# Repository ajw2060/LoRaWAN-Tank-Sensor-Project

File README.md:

# LoRaWAN-Tank-Sensor-Project
Project files including Schematics, PCB Layouts and code for Tank Sensor modules

The following components are included
1)  KiCad schematics and PCB layouts for the Pump Controller, Tank Top Sensor and Remote switch module.
2)  Micro python code for the Pycom LoPy4 based Tank Top Sensor
3)  Python code for the Raspberry Pi based Pump Controller
4)  Python code for the Raspberry Pi Zero W based remote switch module

The code has been zipped to keep the relevant files together.

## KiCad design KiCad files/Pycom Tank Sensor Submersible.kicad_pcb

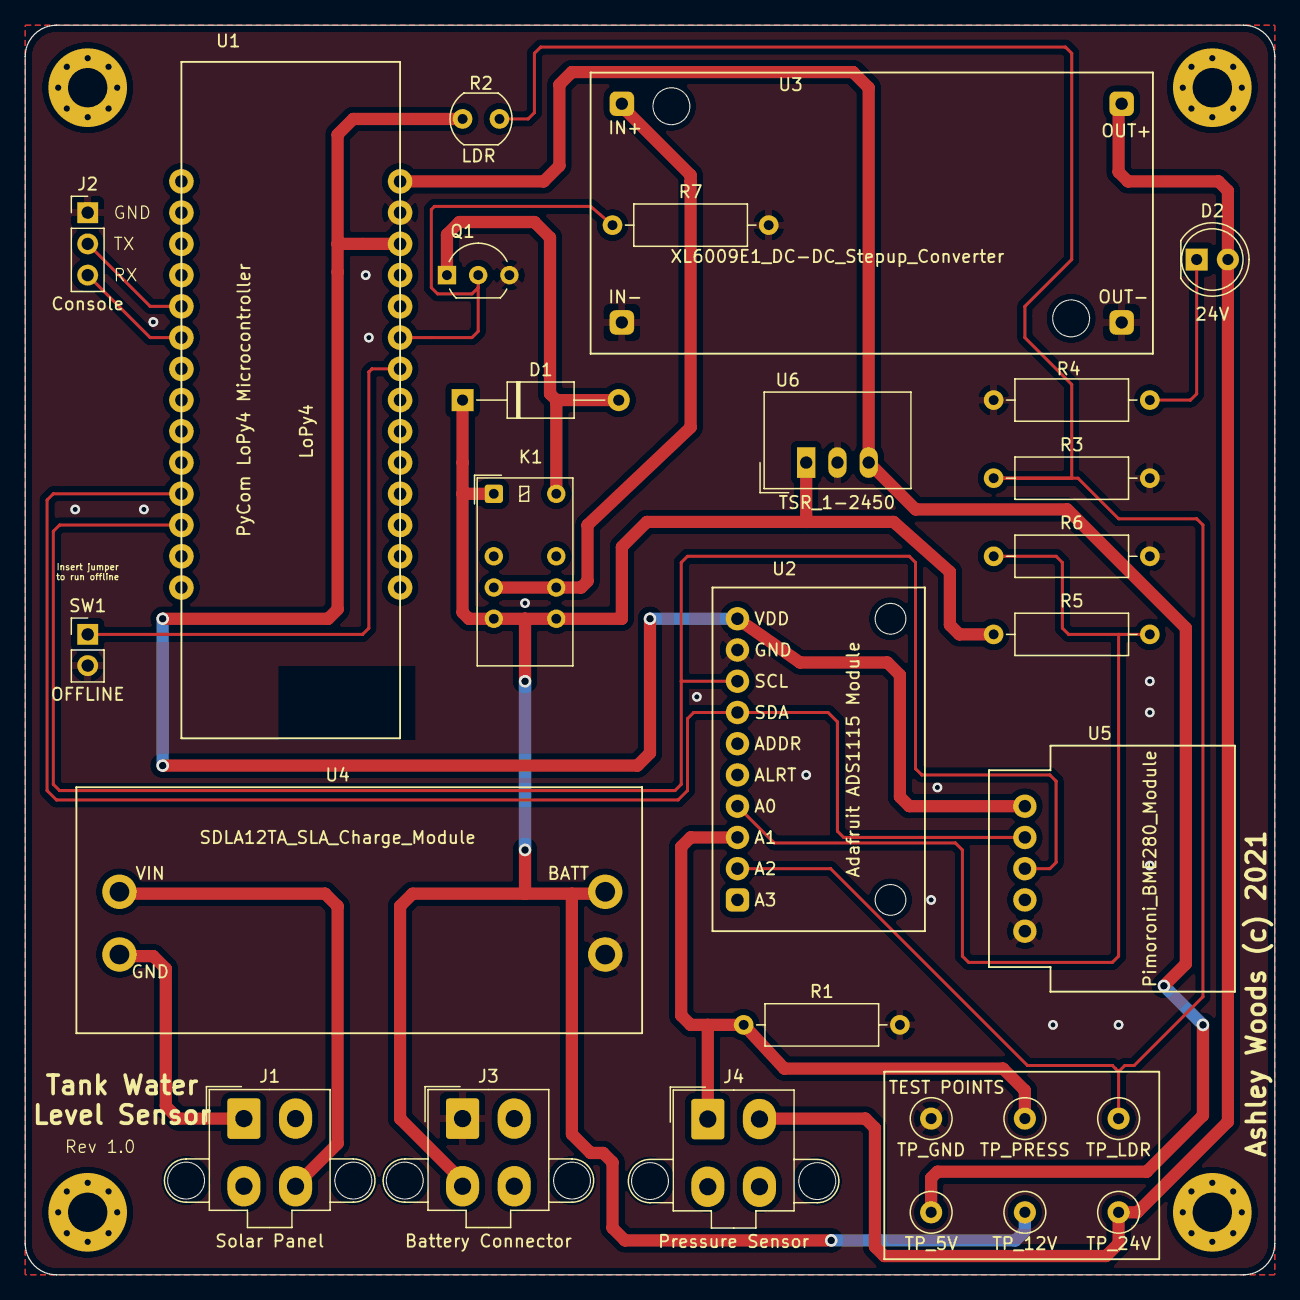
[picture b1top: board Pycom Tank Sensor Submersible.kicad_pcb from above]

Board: 2 copper layers, 101.6 x 101.6 mm, 32 parts (0 on the bottom side), 19 nets.

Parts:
D1: D; D_A-405_P12.70mm_Horizontal
D2: +24 LED; LED_D5.0mm
H1, H2, H3, H4: MountingHole; MountingHole_3.2mm_M3_Pad_Via
J1: Solar Panel; Molex_Mini-Fit_Jr_5566-04A2_2x02_P4.20mm_Vertical
J2: Console; PinHeader_1x03_P2.54mm_Vertical
J3: Battery Connector; Molex_Mini-Fit_Jr_5566-04A2_2x02_P4.20mm_Vertical
J4: Pressure Sensor; Molex_Mini-Fit_Jr_5566-04A2_2x02_P4.20mm_Vertical
J5: TP_GND; TestPoint_Loop_D2.60mm_Drill0.9mm_Beaded
J6: TP_5V; TestPoint_Loop_D2.60mm_Drill0.9mm_Beaded
J7: TP_12V; TestPoint_Loop_D2.60mm_Drill0.9mm_Beaded
J8: TP_24V; TestPoint_Loop_D2.60mm_Drill0.9mm_Beaded
J9: TP_PRESS; TestPoint_Loop_D2.60mm_Drill0.9mm_Beaded
J10: TP_LDR; TestPoint_Loop_D2.60mm_Drill0.9mm_Beaded
K1: EC2-12NU; Relay_DPDT_Kemet_EC2
Q1: BS170; TO-92_Inline_Wide
R1: 100R; R_Axial_DIN0309_L9.0mm_D3.2mm_P12.70mm_Horizontal
R2: LDR; R_LDR_5.0x4.1mm_P3mm_Vertical
R3: 1K; R_Axial_DIN0309_L9.0mm_D3.2mm_P12.70mm_Horizontal
R4: 1.5K; R_Axial_DIN0309_L9.0mm_D3.2mm_P12.70mm_Horizontal
R5: 15K; R_Axial_DIN0309_L9.0mm_D3.2mm_P12.70mm_Horizontal
R6: 4.7K; R_Axial_DIN0309_L9.0mm_D3.2mm_P12.70mm_Horizontal
R7: 10K; R_Axial_DIN0309_L9.0mm_D3.2mm_P12.70mm_Horizontal
SW1: OFFLINE; PinHeader_1x02_P2.54mm_Vertical
U1: LoPy4; LoPy_with_headers
U2: Adafruit_ADS1115_Module
U3: XL6009E1_DC-DC_Stepup_Converter; XL6009E1_DC-DC_Converter
U4: SDLA12TA_SLA_Charge_Module; SDLA12TA_Module
U5: Pimoroni_BME280_Module; Pimoroni BME280 Module
U6: TSR_1-2450; Converter_DCDC_TRACO_TSR-1_THT

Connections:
3v3: R2.1, U1.26, U2.10, U5.1
BATTERY+12: D1.1, J3.3, J7.1, K1.1, K1.5, K1.8, R5.1, U4.4, U6.1
BATTLEVEL_SENSE: R5.2, R6.1, U2.4
BOOST24POS: D2.2, J4.2, J8.1, U3.3
BOOST_ENABLE: Q1.2, R7.1, U1.23
BOOST_SUPPLY: K1.4, K1.9, U3.1
BOOST_SWITCH: D1.2, K1.12, Q1.1
CONSOLE_RX: J2.3, U1.6
CONSOLE_TX: J2.2, U1.5
GND: J2.1, J3.1, J5.1, Q1.3, R1.2, R3.2, R4.2, R6.2, R7.2, SW1.2, U1.27, U2.9, U3.2, U3.4, U4.3, U5.5, U6.2
LDR_SENSE: J10.1, R2.2, R3.1, U2.2
unnamed: D2.1, R4.1
OFFLINE_MODE: SW1.1, U1.22
PANEL_NEG: J1.1, U4.2
PANEL_POS: J1.4, U4.1
PRESS_SENSE: J4.1, J9.1, R1.1, U2.3
SCL: U1.12, U2.8, U5.3
SDA: U1.11, U2.7, U5.2
VCC: J6.1, U1.28, U6.3

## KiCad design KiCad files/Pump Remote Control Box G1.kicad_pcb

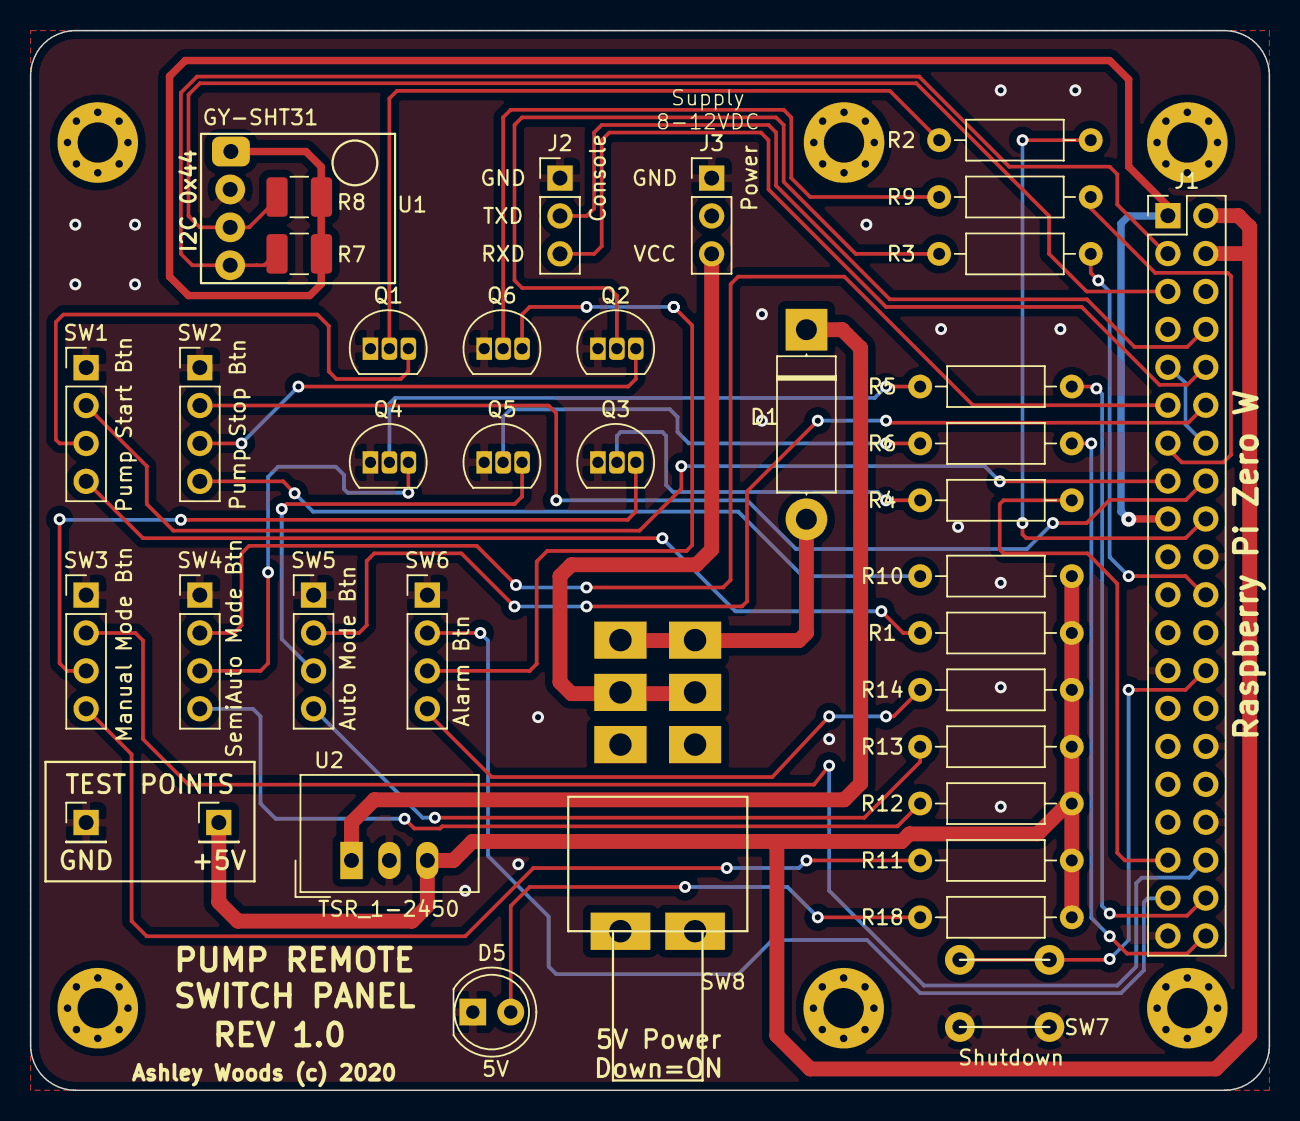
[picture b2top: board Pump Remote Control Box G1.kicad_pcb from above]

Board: 2 copper layers, 83.0 x 71.0 mm, 44 parts (0 on the bottom side), 42 nets.

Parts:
D1: D; D_5W_P12.70mm_Horizontal
D5: 5V; LED_D5.0mm
H1, H2, H3, H4, H5, H6: Mount; MountingHole_2.7mm_M2.5_Pad_Via
J1: Raspberry_Pi_2_3; PinHeader_2x20_P2.54mm_Vertical
J2: Serial Console Connector; PinHeader_1x03_P2.54mm_Vertical
J3: Power Input Connector; PinHeader_1x03_P2.54mm_Vertical
Q1, Q2, Q3, Q4, Q5, Q6: P2N2222A; TO-92L_Inline
R1, R10, R11, R12, R13, R14, R18: 220R; R_Axial_DIN0207_L6.3mm_D2.5mm_P10.16mm_Horizontal
R2, R3, R4, R5, R6, R9: 4k3; R_Axial_DIN0207_L6.3mm_D2.5mm_P10.16mm_Horizontal
R7, R8: 10K; R_1210_3225Metric_Pad1.42x2.65mm_HandSolder
SW1: Pump Start Button; PinHeader_1x04_P2.54mm_Vertical
SW2: Pump Stop Button; PinHeader_1x04_P2.54mm_Vertical
SW3: Manual Mode Button; PinHeader_1x04_P2.54mm_Vertical
SW4: Semiauto Mode Button; PinHeader_1x04_P2.54mm_Vertical
SW5: Auto Mode Button; PinHeader_1x04_P2.54mm_Vertical
SW6: Alarm Button; PinHeader_1x04_P2.54mm_Vertical
SW7: Shutdown; PCB Switch RS 479-1413
SW8: SW_DPDT; Switch DPDT Jaycar ST0365
TP1: TP GND; PinHeader_1x01_P2.54mm_Vertical
TP2: TP +5V; PinHeader_1x01_P2.54mm_Vertical
U1: GY_SHT31-Breakout-pycom; GY_SHT31_Breakout
U2: TSR_1-2450; Converter_DCDC_TRACO_TSR-1_THT

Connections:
3v3: J1.1, J1.17, R7.1, R8.1, U1.1
5V: J1.2, J1.4, R1.1, R10.1, R11.1, R12.1, R13.1, R14.1, R18.2, TP2.1, U2.3
Alarm_Button: J1.37, SW6.2
Alarm_Button_LED: J1.13, R9.2
Auto_Mode_Button: J1.12, SW5.2
Auto_Mode_Button_LED: J1.40, R6.2
GND: D5.1, J1.6, J1.9, J1.14, J1.20, J1.25, J1.30, J1.34, J1.39, J2.1, J3.1, Q1.1, Q2.1, Q3.1, Q4.1, Q5.1, Q6.1, SW1.1, SW2.1, SW3.1, SW4.1, SW5.1, SW6.1, SW7.3, SW7.4, TP1.1, U1.2, U2.2
Manual_Mode_Button: J1.36, SW3.2
Manual_Mode_Button_LED: J1.35, R4.2
unnamed: D1.1, U2.1
unnamed: D1.2, SW8.1, SW8.4
unnamed: D5.2, R18.1
unnamed: J3.3, SW8.2, SW8.5
unnamed: Q1.2, R2.1
unnamed: Q1.3, SW1.3
unnamed: Q2.2, R3.1
unnamed: Q2.3, SW2.3
unnamed: Q3.2, R4.1
unnamed: Q3.3, SW3.3
unnamed: Q4.2, R5.1
unnamed: Q4.3, SW4.3
unnamed: Q5.2, R6.1
unnamed: Q5.3, SW5.3
unnamed: Q6.2, R9.1
unnamed: Q6.3, SW6.3
unnamed: R1.2, SW1.4
unnamed: R10.2, SW2.4
unnamed: R11.2, SW3.4
unnamed: R12.2, SW4.4
unnamed: R13.2, SW5.4
unnamed: R14.2, SW6.4
Pump_Start_Button: J1.15, SW1.2
Pump_Start_Button_LED: J1.18, R2.2
Pump_Stop_Button: J1.16, SW2.2
Pump_Stop_Button_LED: J1.22, R3.2
RXD: J1.10, J2.3
SCL: J1.5, R8.2, U1.3
SDA: J1.3, R7.2, U1.4
SHUTDOWN: J1.26, SW7.1, SW7.2
Semiauto_Mode_Button: J1.11, SW4.2
Semiauto_Mode_Button_LED: J1.38, R5.2
TXD: J1.8, J2.2

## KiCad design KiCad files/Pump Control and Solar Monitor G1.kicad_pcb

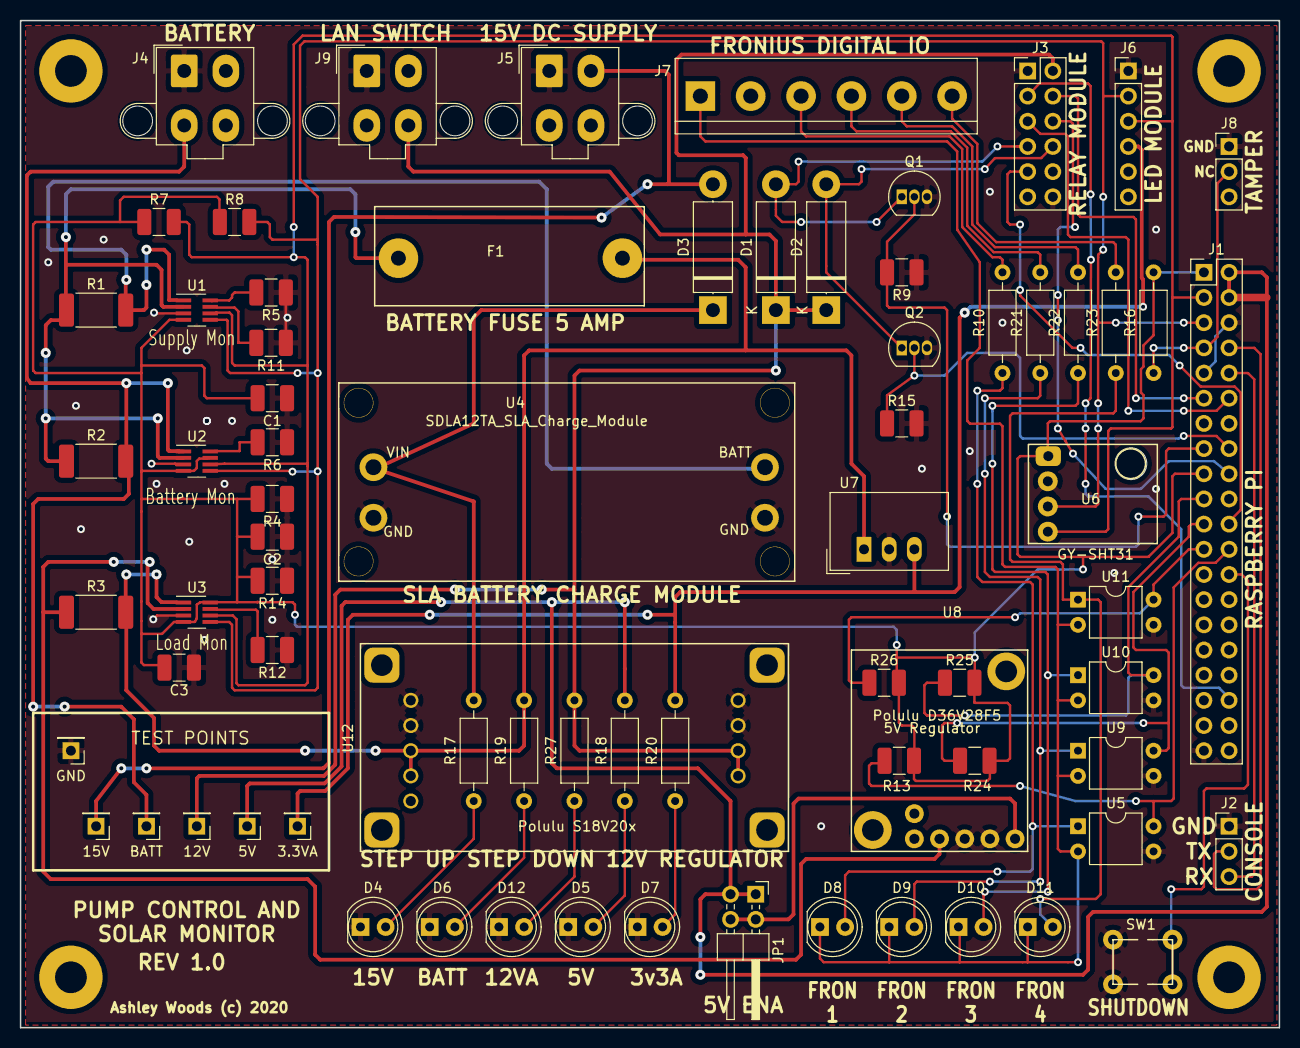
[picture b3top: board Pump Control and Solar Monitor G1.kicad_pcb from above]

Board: 2 copper layers, 127.0 x 101.6 mm, 74 parts (0 on the bottom side), 50 nets.

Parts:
C1, C2, C3: 0.1uF; C_1210_3225Metric_Pad1.42x2.65mm_HandSolder
D1, D2: FLYBACK DIODE; D_5W_P12.70mm_Horizontal
D3: Polarity Protection; D_5W_P12.70mm_Horizontal
D4: 15V Present; LED_D5.0mm
D5: 5V Present; LED_D5.0mm
D6: BATTERY Present; LED_D5.0mm
D7: 3v3AUX Present; LED_D5.0mm
D8: Fron1; LED_D5.0mm
D9: Fron2; LED_D5.0mm
D10: Fron3; LED_D5.0mm
D11: Fron4; LED_D5.0mm
D12: 12VA Supply; LED_D5.0mm
F1: Fuse 5 AMP; Wuth Electronik PCB TTH Fuse Holder
J1: Raspberry_Pi_2_3; PinHeader_2x20_P2.54mm_Vertical
J2: Serial Console Connector; PinHeader_1x03_P2.54mm_Vertical
J3: Switch Module Connector; PinHeader_2x06_P2.54mm_Vertical
J4: Battery Connector; Molex_Mini-Fit_Jr_5566-04A2_2x02_P4.20mm_Vertical
J5: DC Power Supply Conector; Molex_Mini-Fit_Jr_5566-04A2_2x02_P4.20mm_Vertical
J6: LED Module Connector; PinHeader_1x06_P2.54mm_Vertical
J7: Plug in Screw_Terminal; TerminalBlock_bornier-6_P5.08mm
J8: Tamper Switch Connector; PinHeader_1x03_P2.54mm_Vertical
J9: Netgear Power; Molex_Mini-Fit_Jr_5566-04A2_2x02_P4.20mm_Vertical
JP1: 5V Enable Jumper; PinHeader_2x02_P2.54mm_Horizontal_DualConnected
Q1, Q2: BS170; TO-92_Inline
R1, R2, R3: 0.1R; R_2512_6332Metric_Pad1.52x3.35mm_HandSolder
R4, R5, R6, R7, R8, R9, R11, R12, R13, R14, R15, R24, R25, R26: 10K; R_1210_3225Metric_Pad1.42x2.65mm_HandSolder
R10, R21, R22, R23: 540R; R_Axial_DIN0207_L6.3mm_D2.5mm_P10.16mm_Horizontal
R16: 10K; R_Axial_DIN0207_L6.3mm_D2.5mm_P10.16mm_Horizontal
R17, R20: 1K; R_Axial_DIN0207_L6.3mm_D2.5mm_P10.16mm_Horizontal
R18: 220R; R_Axial_DIN0207_L6.3mm_D2.5mm_P10.16mm_Horizontal
R19, R27: 820R; R_Axial_DIN0207_L6.3mm_D2.5mm_P10.16mm_Horizontal
SW1: PCB_Switch_RS479-1413; PCB Switch RS 479-1413
TP1: TP GND; PinHeader_1x01_P2.54mm_Vertical
TP2: TP 15V; PinHeader_1x01_P2.54mm_Vertical
TP3: TP Battery; PinHeader_1x01_P2.54mm_Vertical
TP4: TP 12VA; PinHeader_1x01_P2.54mm_Vertical
TP5: TP 5V; PinHeader_1x01_P2.54mm_Vertical
TP6: TP 3v3A; PinHeader_1x01_P2.54mm_Vertical
U1, U2, U3: INA219AIDCNR; SOT-23-8_Handsoldering
U4: SDLA12TA_SLA_Charge_Module; SDLA12TA_Module
U5, U9, U10, U11: PC817; DIP-4_W7.62mm
U6: GY_SHT31 Module; GY_SHT31_Breakout
U7: TSR_1-2433; Converter_DCDC_TRACO_TSR-1_THT
U8: Polulu D36V28F5 5V Regulator; Polulu_D36V28F5_Regulator
U12: Polulu_S18V20F12_Voltage_Regulator; Polulu_S18V20x_Regulators

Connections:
3v3: C1.2, C2.2, C3.2, J1.1, J1.17, R4.2, R7.1, R8.1, R13.2, R14.2, R16.2, R24.2, R25.2, R26.2, U1.4, U2.4, U2.7, U3.4, U3.8, U6.1
5V: J1.2, J1.4, JP1.1, R18.2, TP5.1
+3.3VA: J6.4, R20.2, TP6.1, U7.3
+12VA: D1.1, D2.1, J3.2, J9.4, R27.2, TP4.1, U12.6, U12.7
+15V: D3.1, R17.2, U4.1
AC_Phase1_Present: J1.36, J3.3
AC_Phase2_Present: J1.11, J3.4
AC_Phase3_Present: J1.12, J3.5
BATTERY+: J4.3, R2.2, TP3.1, U2.1
BATTERY_SUPPLY: F1.1, R3.2, R19.2, U3.1, U7.1, U12.3, U12.4
FRONIUS_1: J1.24, R13.1, U5.4
FRONIUS_2: J1.21, R24.1, U9.4
FRONIUS_3: J1.19, R25.1, U10.4
FRONIUS_4: J1.23, R26.1, U11.4
FRONIUS_GND: D8.1, D9.1, D10.1, D11.1, J7.1, U5.2, U9.2, U10.2, U11.2
FRONIUS_RAW_1: J7.3, R10.2
FRONIUS_RAW_2: J7.4, R21.2
FRONIUS_RAW_3: J7.5, R22.2
FRONIUS_RAW_4: J7.6, R23.2
GND: C1.1, C2.1, C3.1, D4.1, D5.1, D6.1, D7.1, D12.1, J1.6, J1.9, J1.14, J1.20, J1.25, J1.30, J1.34, J1.39, J2.1, J3.1, J3.12, J4.1, J5.1, J6.1, J8.1, J9.1, Q1.3, Q2.3, R4.1, R5.1, R6.1, R9.1, R11.1, R12.1, R14.1, R15.2, SW1.3, SW1.4, TP1.1, U1.3, U2.3, U3.3, U4.2, U4.3, U5.3, U6.2, U7.2, U8.4, U8.5, U9.3, U10.3, U11.3, U12.1, U12.2, U12.8, U12.9
unnamed: D3.2, J5.2, TP2.1
unnamed: D4.2, R17.1
unnamed: D5.2, R18.1
unnamed: D6.2, R19.1
unnamed: D7.2, R20.1
unnamed: D8.2, R10.1, U5.1
unnamed: D9.2, R21.1, U9.1
unnamed: D10.2, R22.1, U10.1
unnamed: D11.2, R23.1, U11.1
unnamed: D12.2, R27.1
unnamed: F1.2, R1.1, R2.1, U1.2, U2.2
unnamed: JP1.2, U8.6
unnamed: R1.2, U1.1, U4.4
unnamed: R3.1, U3.2, U8.3
unnamed: R5.2, U1.8
unnamed: R6.2, U2.8
unnamed: R11.2, U1.7
unnamed: R12.2, U3.7
PUMP_FAULT: J1.22, J3.9
PUMP_RUNNING: J1.18, J3.6
PUMP_START_PULSE: J1.15, Q1.2, R9.2
PUMP_START_RELAY: D1.2, J3.7, Q1.1
PUMP_STOP_PULSE: J1.16, Q2.2, R15.1
PUMP_STOP_RELAY: D2.2, J3.8, Q2.1
RXD: J1.10, J2.3
SCL: J1.5, J6.2, R8.2, U1.5, U2.5, U3.5, U6.3
SDA: J1.3, J6.3, R7.2, U1.6, U2.6, U3.6, U6.4
SHUTDOWN: J1.26, SW1.1, SW1.2
TAMPER: J1.7, J8.2, R16.1
TXD: J1.8, J2.2

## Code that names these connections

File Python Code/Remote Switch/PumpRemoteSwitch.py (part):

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

# ---- Define the GPIO pins used by each button
manual_mode_button = Button(16, bounce_time=0.05)           # Pin 36
semiauto_mode_button = Button(17, bounce_time=0.05)	        # Pin 11
automatic_mode_button = Button(18, bounce_time=0.05)        # Pin 12
pump_start_button = Button(22)                              # Pin 15  Seems to work better with no debounce
pump_stop_button = Button(23)                               # Pin 16
alarm_button = Button(26, bounce_time=0.05)                 # Pin 37

# ---- Define the GPIO pins used by the LEDs inside the buttons
pump_start_button_led = LED(24, active_high=True, initial_value=False, pin_factory=None)        # Pin 18
pump_stop_button_led = LED(25, active_high=True, initial_value=False, pin_factory=None)         # Pin 22
manual_mode_button_led = LED(19, active_high=True, initial_value=False, pin_factory=None)       # Pin 35
semiauto_mode_button_led = LED(20, active_high=True, initial_value=False, pin_factory=None)     # Pin 38
auto_mode_button_led = LED(21, active_high=True, initial_value=False, pin_factory=None)         # Pin 40
alarm_button_led = LED(27, active_high=True, initial_value=False, pin_factory=None)             # Pin 13



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
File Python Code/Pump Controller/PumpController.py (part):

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

# ---- Define the GPIO pins used by each sense or control line
# The shutdown_button on GPIO7 (Pin 26) is not initialised here as it is used in the separate shutdown script.
phase1_present_sense = Button(16)       #Pin 36
phase2_present_sense = Button(17)       #Pin 11
phase3_present_sense = Button(18)       #Pin 12
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fronius_digital3_sense = Button(10)     #Pin 19
fronius_digital4_sense = Button(11)     #Pin 23

pump_start_pulse = OutputDevice(22, active_high=True, initial_value=False, pin_factory=None)       #Pin 15
pump_stop_pulse = OutputDevice(23, active_high=True, initial_value=False, pin_factory=None)        #Pin 16



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
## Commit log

2021-09-29 Add files via upload
    KiCad Schematics and PCB layout files
2021-09-29 Add files via upload
    Python and micropython code for each component

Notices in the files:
KiCad files/Pump Control and Solar Monitor G1.kicad_pcb:
Ashley Woods (c) 2020
KiCad files/Pycom Tank Sensor Submersible.kicad_pcb:
Ashley Woods (c) 2021
